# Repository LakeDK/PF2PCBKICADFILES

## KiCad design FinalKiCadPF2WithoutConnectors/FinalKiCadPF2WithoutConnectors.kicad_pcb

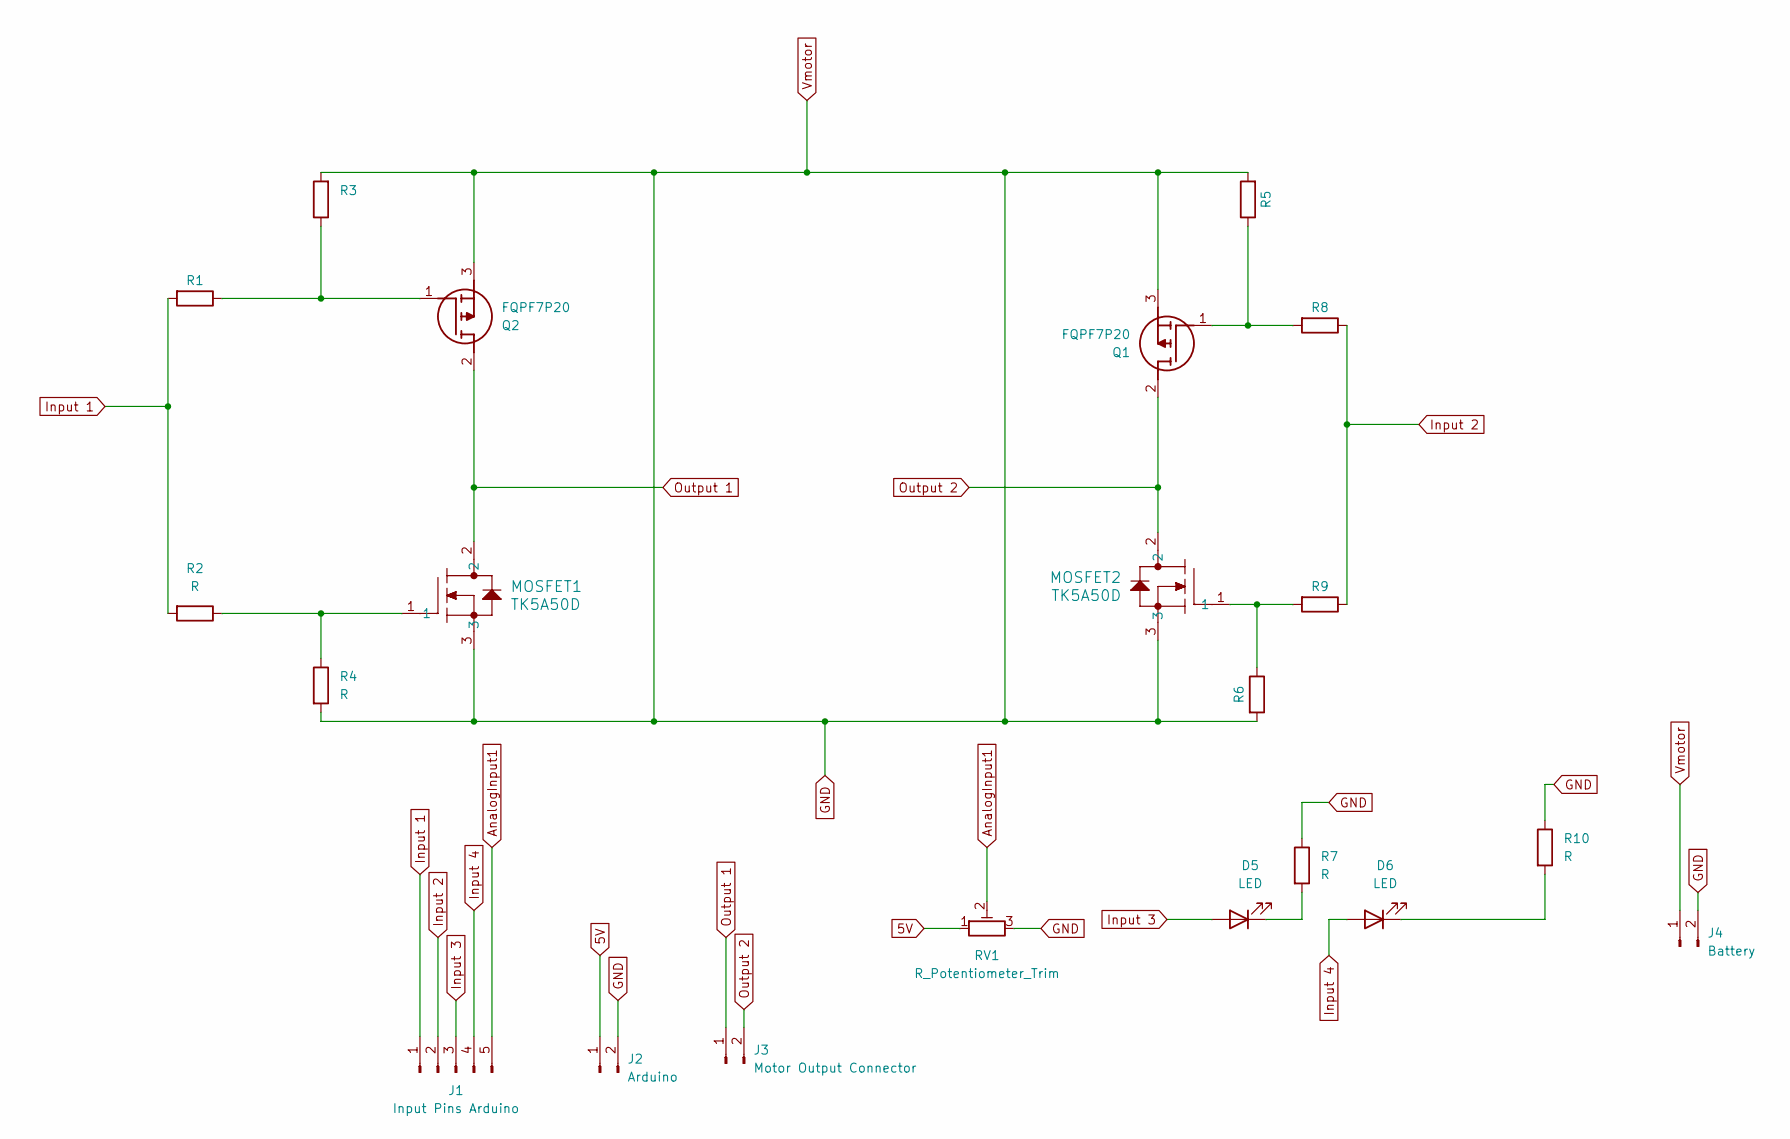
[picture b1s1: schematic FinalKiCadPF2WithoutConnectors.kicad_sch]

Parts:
D5, D6: LED; LED_D3.0mm_Horizontal_O1.27mm_Z2.0mm
J1: Input Pins Arduino; PinHeader_1x05_P2.54mm_Vertical
J2: Arduino; PinHeader_1x02_P2.54mm_Vertical
J3: Motor Output Connector; PinHeader_1x02_P2.54mm_Vertical
J4: Battery; PinHeader_1x02_P2.54mm_Vertical
MOSFET1, MOSFET2: TK5A50D; TO-220SIS_TOS
Q1, Q2: FQPF7P20; TO254P274X1016X1970-3P; Manufacturer_Part_Number FQPF7P20
R1, R2, R3, R4, R5, R6, R7, R8, R9, R10: R; R_Axial_DIN0207_L6.3mm_D2.5mm_P10.16mm_Horizontal
RV1: R_Potentiometer_Trim; Potentiometer_Bourns_3296Y_Vertical

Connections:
5V: J2.1, RV1.1
AnalogInput1: J1.5, RV1.2
GND: J2.2, J4.1, J4.2, MOSFET1.3, MOSFET2.3, Q1.3 (S), Q2.3 (S), R3.2, R4.2, R5.2, R6.2, R7.1, R10.1, RV1.3
Input 1: J1.1, R1.2, R2.2
Input 2: J1.2, R8.1, R9.1
Input 3: D5.2 (A), J1.3
Input 4: D6.2 (A), J1.4
unnamed: D5.1 (K), R7.2
unnamed: D6.1 (K), R10.2
unnamed: MOSFET1.1, R2.1, R4.1
unnamed: MOSFET2.1, R6.1, R9.2
unnamed: Q1.1 (G), R5.1, R8.2
unnamed: Q2.1 (G), R1.1, R3.1
Output 1: J3.1, MOSFET1.2, Q2.2 (D)
Output 2: J3.2, MOSFET2.2, Q1.2 (D)

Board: 2 copper layers, 21 parts (0 on the bottom side), 15 nets, no tracks yet.

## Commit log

2024-06-06 PUSHING FILES FOR PRINTING TOMORROW
    1.REMEMBER TO ROUTE
    2.CHECK ANY FOR ERRORS
2024-06-07 LIibrary Added
